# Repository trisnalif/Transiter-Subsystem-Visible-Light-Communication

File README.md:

# Transmiter-Subsystem-Visible-Light-Communication

Hardware design repository (KiCad schematic and PCB layout) for a high-speed **Visible Light Communication (VLC) Transmitter Subsystem**. The circuit integrates a DC bias-tee conditioning network, a high-speed non-inverting amplifier stage based on dual **LM7171BIN** op-amps, and an **IRF510PBF** N-channel power MOSFET driver stage to modulate an LED light source with high-frequency data signals.

---

#### Circuit Architecture & Functional Blocks

1. **Power Supply Decoupling & DC Bias Reference (`C3`, `JP1`, `RV1`, `C2`, `U1`)**
   - **`C3` (2.2 µF):** Bulk decoupling capacitor connected between `VCC` and `GNDREF` to filter low-frequency supply ripple.
   - **`RV1` (Trim Potentiometer) & `C2` (100 nF):** Forms an adjustable voltage divider (enabled via solder jumper `JP1`) with high-frequency noise filtering (`C2`) to set the precise DC offset voltage required to keep the transmitter LED operating in its linear region.
   - **`U1` (LM7171BIN — Voltage Follower / Buffer):** Configured as a unity-gain buffer (`OUT` tied directly to `-IN`) to provide a low-impedance, stable DC bias reference without loading the potentiometer network.

2. **Passive Bias-Tee & Signal Combining Network (`J1`, `R2`, `R3`, `C4`)**
   - **`J1` (Coaxial / RF Input Connector `10-473-A3`):** Accepts the incoming high-speed modulating data signal.
   - **`R2` (510 Ω) & `R3` (1 kΩ):** Resistive summing network that combines the buffered DC bias voltage from `U1` with the AC data signal from `J1` before feeding into the amplification stage.
   - **`C4` (10 pF):** Shunt capacitor to `GNDREF` for high-frequency stability and parasitic ringing suppression.

3. **High-Speed Gain Stage (`U2`, `R4`, `R5`)**
   - **`U2` (LM7171BIN — Non-Inverting Amplifier):** A very high-speed, high-slew-rate voltage-feedback operational amplifier configured in a non-inverting topology to amplify the combined DC + AC signal.
   - **`R4` (510 Ω) & `R5` (510 Ω):** Feedback resistor network setting a closed-loop voltage gain off, preserving fast signal transitions.

4. **LED Driver & Output Modulation Stage (`R6`, `C1`, `Q1`, `JP2`)**
   - **`R6` (47 Ω) & `C1` (20 pF):** Gate resistor and shunt capacitance placed between `U2` output and the MOSFET gate to damp high-frequency oscillations and control switching edge rates.
   - **`Q1` (IRF510PBF — N-Channel Power MOSFET):** Acts as the current-modulating driver stage (Drain connected to `VCC` / LED load path, Source routed through jumper `JP2` to `GNDREF`) capable of handling higher LED drive currents at high switching speeds.
   - **`JP1` & `JP2` (Bridged Jumpers):** Hardware test/isolation jumpers allowing easy current measurement or circuit debugging during PCB bring-up.

---

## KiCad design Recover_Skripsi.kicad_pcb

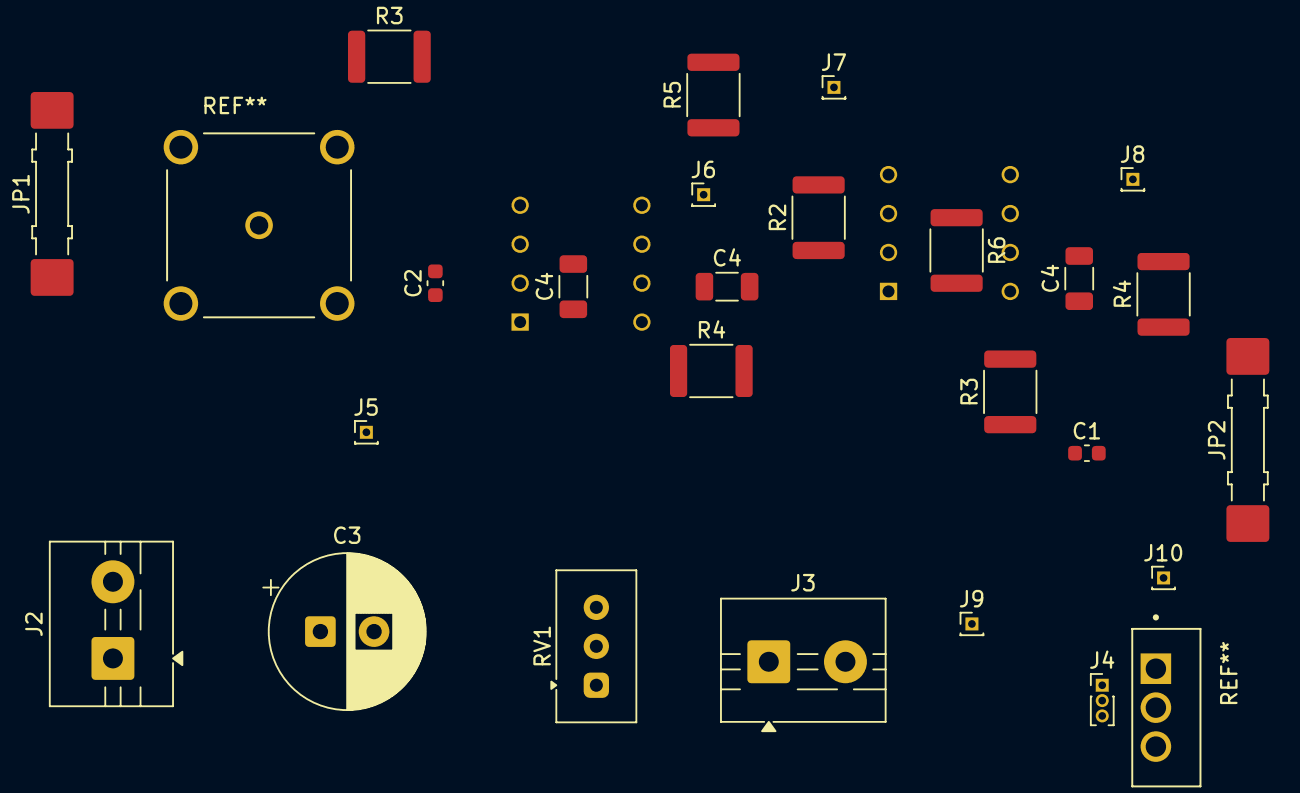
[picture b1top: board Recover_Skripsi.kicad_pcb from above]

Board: 2 copper layers, 25 parts (0 on the bottom side), 9 nets, no tracks yet.

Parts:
C1: 20pF; C_0603_1608Metric
C2: 100nF; C_0603_1608Metric
C3: 2.2uF; CP_Radial_D10.0mm_P3.50mm
C4, C4#2, C4#3: 10pF; C_1206_3216Metric
J2, J3: Screw_Terminal_01x02; TerminalBlock_MaiXu_MX126-5.0-02P_1x02_P5.00mm
J4: Pinheader2; PinHeader_1x03_P1.00mm_Vertical
J5: TP1; PinHeader_1x01_P1.00mm_Vertical
J6: TP2; PinHeader_1x01_P1.00mm_Vertical
J7: TP3; PinHeader_1x01_P1.00mm_Vertical
J8: TP5; PinHeader_1x01_P1.00mm_Vertical
J9: TP4; PinHeader_1x01_P1.00mm_Vertical
J10: TP6; PinHeader_1x01_P1.00mm_Vertical
JP1, JP2: Jumper_2_Bridged; Jumper_Harwin_S1621_P10.9mm
R2, R4, R4#2, R5: 510; R_1812_4532Metric
R3, R3#2: 1k; R_1812_4532Metric
R6: 47; R_1812_4532Metric
RV1: R_Potentiometer_Trim; Potentiometer_Vishay_T93YA_Vertical

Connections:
GNDREF: C1.2, C2.2, C3.2, C4.2, C4#3.2, J3.1 (Pin_1_1), JP1.2 (B), JP2.2 (B), R3.2, R4.1, R4#2.1, RV1.3
unnamed: C3.1, J2.1 (Pin_1_1), J4.1, J9.1 (Pin_1_1), JP1.1 (A), RV1.1
unnamed: C1.1, J4.2, R6.2
unnamed: C2.1, J5.1 (Pin_1_1), RV1.2
unnamed: C4#3.1, J6.1 (Pin_1_1), R2.1
unnamed: J7.1 (Pin_1_1), R2.2, R3.1
unnamed: J8.1 (Pin_1_1), R5.2, R6.1
unnamed: J4.3, J10.1 (Pin_1_1), JP2.1 (A)
unnamed: R4.2, R4#2.2, R5.1
